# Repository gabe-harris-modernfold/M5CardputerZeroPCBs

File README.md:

# M5CardputerZeroPCBs

KiCad tooling for preparing PCB orders, driven from Claude Code through MCP servers.

## What's here

| Path | What it is |
| --- | --- |
| [`LightSensingPCB`](LightSensingPCB/README.md) | Cap carrying an Adafruit AS7343 14-channel spectral sensor breakout |
| [`BreadPortZero`](BreadPortZero/README.md) | Breakout cap: I2C (4 STEMMA QT / Qwiic, 2 sockets) on its own bus, buffered SPI, UART, 4 analog inputs (ADS1115) and USB-C supplemental power, with current limiting, a FAULT LED, a software power switch, I2C isolation and ESD protection for the host |
| [`tools/gerber_check`](tools/gerber_check/README.md) | `gerber-check`: checks Gerber and drill output against PCBWay and JLCPCB rules, lints the board and assembly files, and writes a ready-to-upload order package with an order sheet |
| `.mcp.json` | Registers three MCP servers for Claude Code: `kicad` (kicad-mcp-pro), `kicad-mixelpixx` (KiCAD-MCP-Server) and `gerber-check` |

## Setup (Windows)

- KiCad 10 installed in the default location (`kicad-cli` is used for exports and DRC). `gerber-check` and BreadPortZero's
  generators also find the per-user install that `winget install KiCad.KiCad` makes (`%LOCALAPPDATA%\Programs\KiCad\10.0`).
- [uv](https://docs.astral.sh/uv/) on `PATH`. `gerber-check` starts with `uv run`, which installs its dependencies on first use.
- Optional: `kicad-mcp-pro` installed with `uv tool install` (expected in `%USERPROFILE%\.local\bin`), and
  [KiCAD-MCP-Server](https://github.com/mixelpixx/KiCAD-MCP-Server) built in `C:\SourceCode\KiCAD-MCP-Server`.
- The paths in `.mcp.json` assume this repository is cloned to `C:\SourceCode\M5CardputerZeroPCBs`. Edit them if yours differs.

kicad-mcp-pro's first start can take about a minute, which is longer than Claude Code's default 30 s MCP startup
timeout. Set `MCP_TIMEOUT` (milliseconds) higher if it fails to connect.

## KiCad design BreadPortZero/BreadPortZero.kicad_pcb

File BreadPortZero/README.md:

# BreadPortZero

A cap for the M5Stack CardputerZero's top expansion port that adds:
- an I2C bus on four STEMMA QT / Qwiic connectors and two 0.1 in sockets;
- an SPI socket (SPI0, chip select CE1), buffered;
- a UART socket;
- four analog inputs, from an on-board ADS1115 ADC, with unfitted divider pads for 5 V signals;
- a USB-C jack for extra power: about 1 A at 3.3 V instead of about 220 mA from the host.

The host is protected in five ways:
- a current-limited power switch (234-303 mA), with a FAULT LED that lights while it limits, and a second one
  (1.09-1.26 A) on the USB input; a power mux connects only one source at a time, so neither can back-feed the other;
- an I2C isolator with ESD protection;
- an SPI buffer that keeps breadboard wiring off the display's bus and drops off it when the cap is unpowered;
- ESD protection on the SPI and UART lines, series resistors on the UART, series resistors and filter capacitors on
  the analog inputs;
- its own I2C bus on G22/G23, so external devices can't disturb the host's keyboard bus.

USB only powers the cap while the host's ExtPort 5 V is on. Bridge JP9 and a script can power-cycle everything plugged
in by driving G7 high (then the SPI socket can't be used).

The bottom silkscreen is the board's manual: setup steps (including the `config.txt` line), a ports table, the host
pinout beside every J1 pin, what each jumper does, a power-path diagram and what the LEDs mean.

See [SPEC.md](SPEC.md) for the design, pinout, solder jumpers, BOM and cost.

## Host setup

BreadPortZero's I2C bus is a software bus on G22 (SDA) / G23 (SCL). Add this to `/boot/firmware/config.txt`, reboot, and
turn on Settings > ExtPort:

```
dtoverlay=i2c-gpio,bus=3,i2c_gpio_sda=22,i2c_gpio_scl=23
```

The bus is `/dev/i2c-3`, and the ADS1115 answers at 0x48 (`i2cdetect -y 3`).

To put the bus on the host's I2C1 instead:
- Bridge JP1 and JP2.
- Cut JP8.
- Leave out the overlay.

To let software power-cycle the cap (for example to reset a hung I2C board), bridge JP9 and drive G7:

```
pinctrl set 7 op dh    # off
pinctrl set 7 op dl    # on
```

Hold it off for about a second so the rails drain. G7 is also the SPI socket's chip select (SPI0 CE1), which idles
high, so JP9 and SPI exclude each other: with JP9 bridged, keep the SPI driver off G7 (for example
`dtoverlay=spi0-1cs`).

The SPI socket is SPI0's CE1 (`/dev/spidev0.1`, if the host's image creates it alongside the display on CE0). Its
pins, left to right: GND, 3V3, SCK, MOSI, CS, MISO.

For more than about 220 mA at 3.3 V, plug a USB-C charger into the jack on the right end (power only; up to about 1 A
at 3.3 V). ExtPort 5 V must still be on.

The other jumpers are listed in [SPEC.md](SPEC.md#solder-jumpers).

## Files

| File | What it is |
| --- | --- |
| `BreadPortZero.kicad_pro`, `.kicad_sch`, `.kicad_pcb` | KiCad 10 project (generated; open and edit as usual) |
| `BreadPortZero.kicad_sym`, `sym-lib-table` | Project symbol library (TPS2553, TPS2116, TLV62569, 74LVC125: KiCad doesn't ship them in this form) |
| `BreadPortZero.pretty`, `fp-lib-table` | Project footprint library: the USB-C jack's KiCad footprint with fab-rule fixes |
| `tools/design.py` | Board size, pin maps, socket positions, parts and nets: the single source for both generators |
| `tools/gen_schematic.py` | Writes the schematic from `design.py` |
| `tools/gen_pcb.py` | Writes the PCB: placement, routing, fiducials, GND pours and silkscreen (including the bottom's reference text) |
| `tools/make_footprints.py` | Writes `BreadPortZero.pretty` from KiCad's stock footprints (run with KiCad's Python) |

## Rebuild

The scripts find KiCad 10 in `C:\Program Files\KiCad\10.0` or in the per-user location winget installs to
(`%LOCALAPPDATA%\Programs\KiCad\10.0`). Set `KICAD_DIR` to use another install.

```powershell
python tools\gen_schematic.py
```

```powershell
& "$env:LOCALAPPDATA\Programs\KiCad\10.0\bin\python.exe" tools\gen_pcb.py
```

Then check it:

```powershell
& "$env:LOCALAPPDATA\Programs\KiCad\10.0\bin\kicad-cli.exe" sch erc --severity-all BreadPortZero.kicad_sch
```

```powershell
& "$env:LOCALAPPDATA\Programs\KiCad\10.0\bin\kicad-cli.exe" pcb drc --schematic-parity --severity-all BreadPortZero.kicad_pcb
```

Regenerating overwrites hand edits to the schematic and PCB. Once you start editing in KiCad, stop using the generators.

The pictures in `docs/` are KiCad renders. `--side bottom` gives the bottom view; the 3D view is 952 high with
`--perspective --rotate "-45,0,20" --zoom 1.45`:

```powershell
& "$env:LOCALAPPDATA\Programs\KiCad\10.0\bin\kicad-cli.exe" pcb render --side top -w 1736 -h 504 --quality high --floor --zoom 1.9 -o docs\board-top.png BreadPortZero.kicad_pcb
```

Fab output comes from the `gerber-check` MCP server's `export_for_fab` tool (profile `jlcpcb_standard` or
`pcbway_standard`), which writes to `fab/<profile>/`.

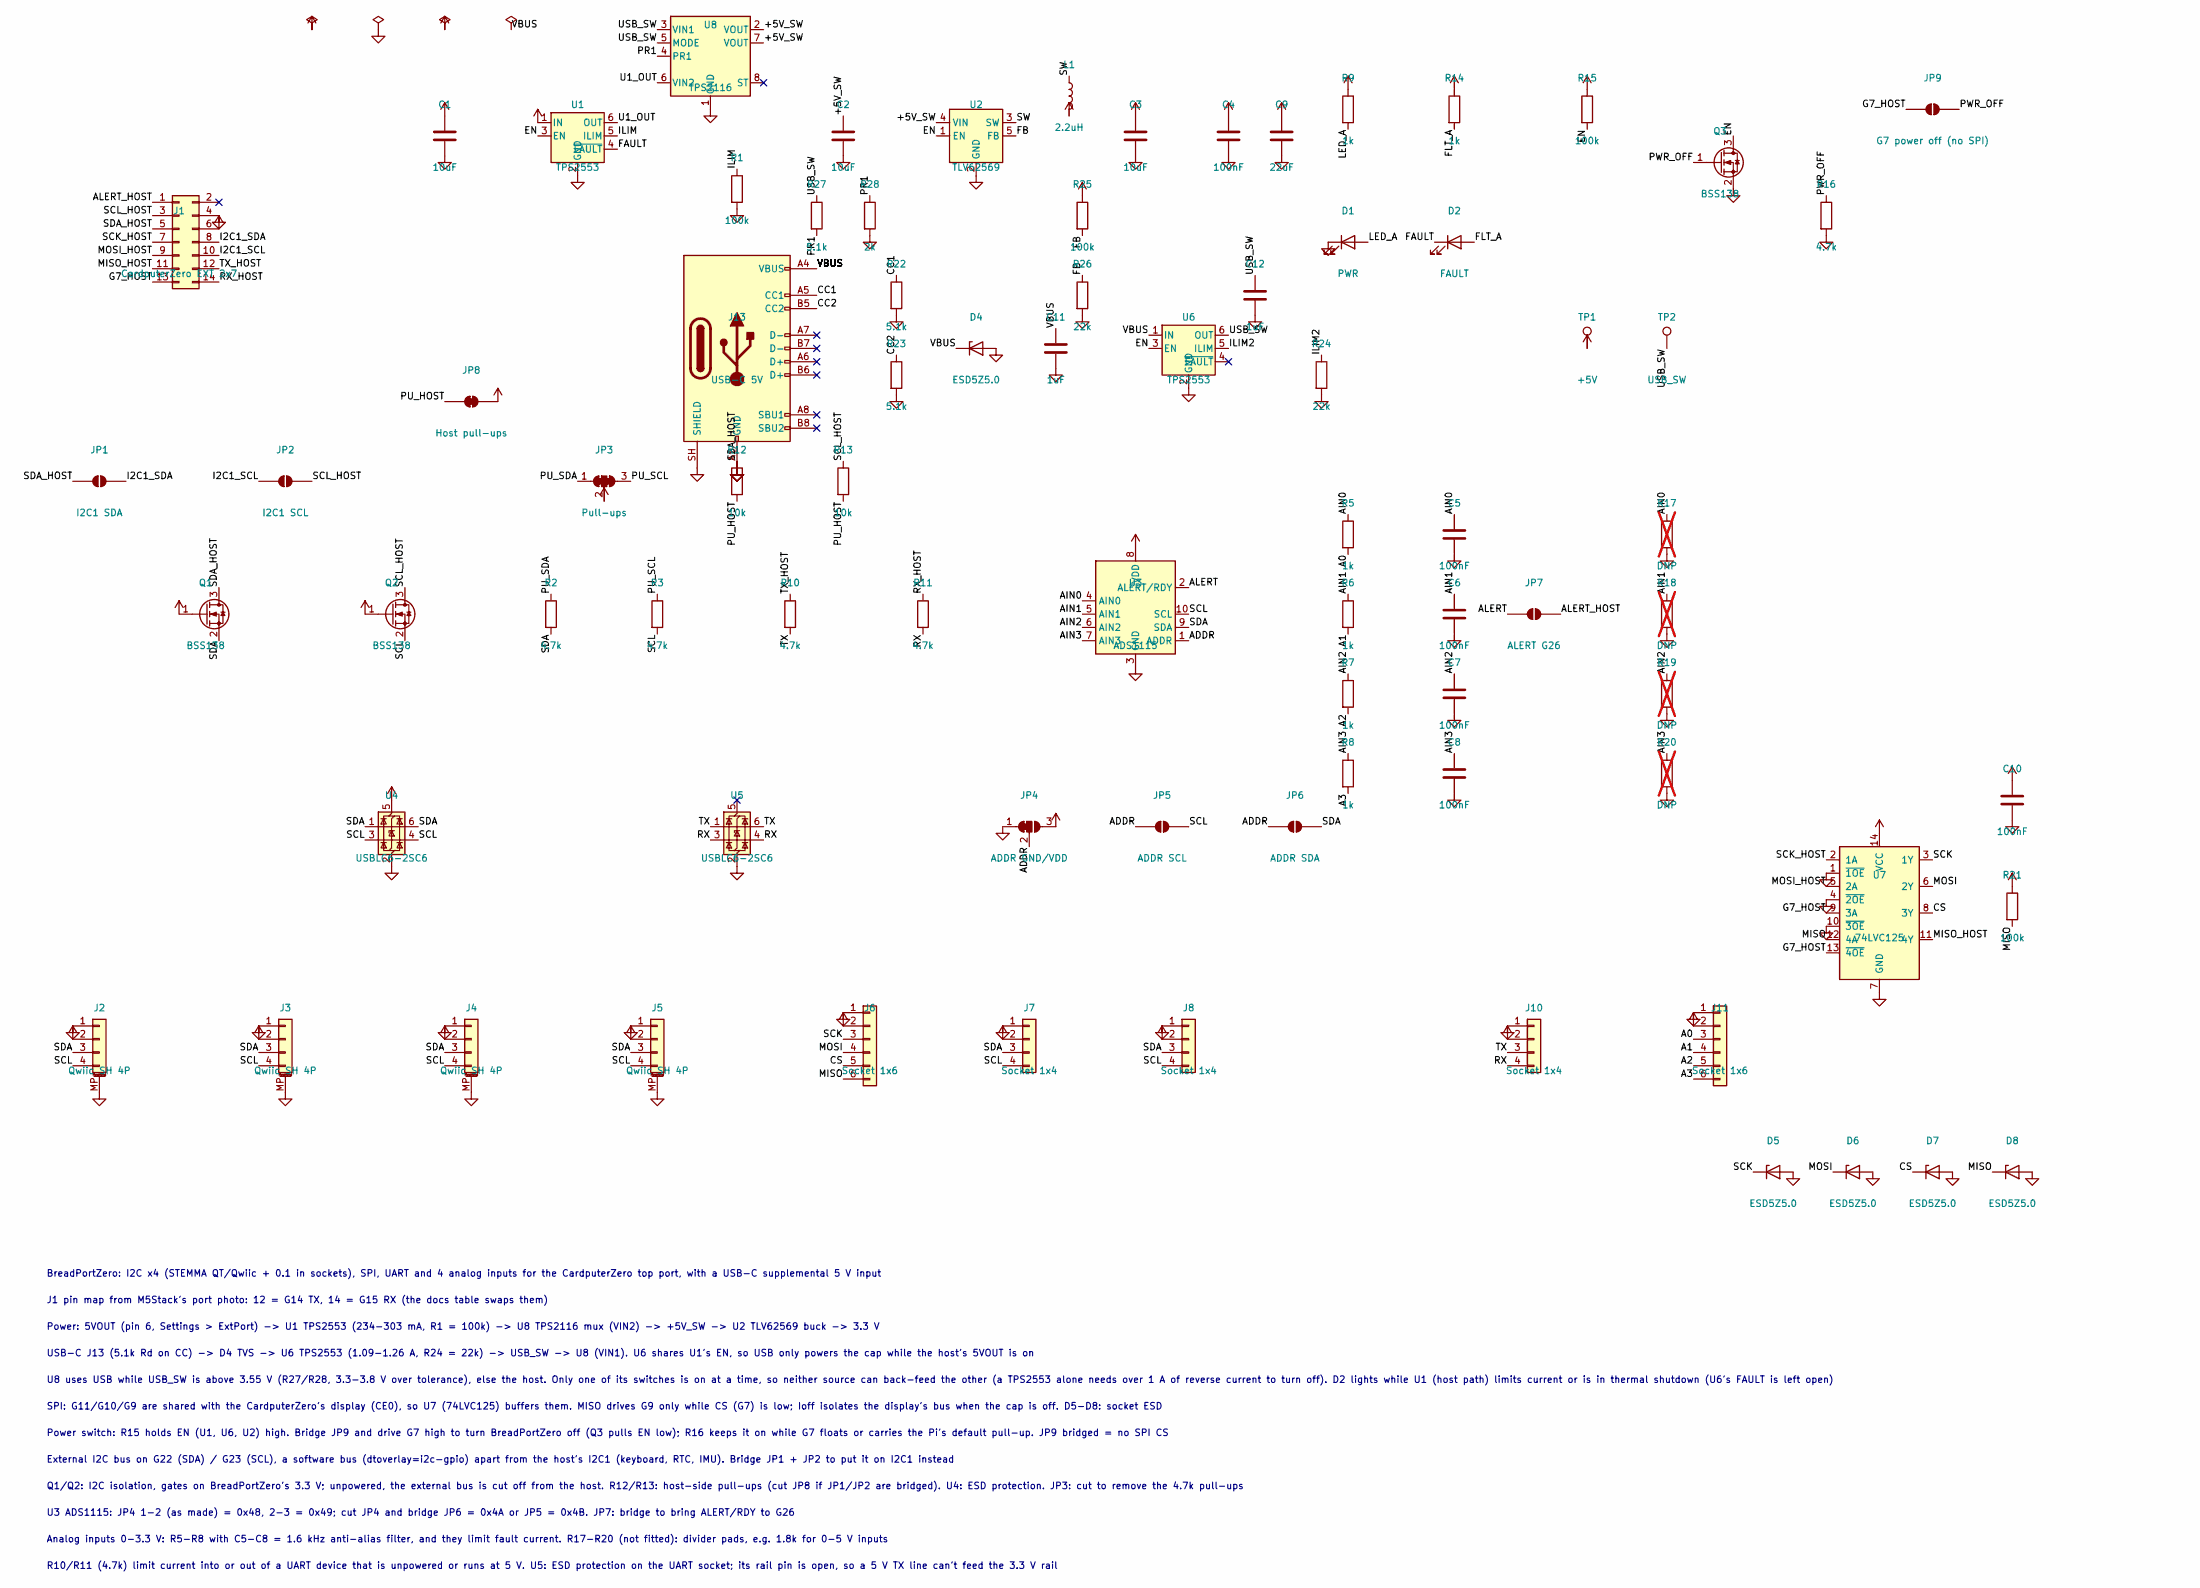
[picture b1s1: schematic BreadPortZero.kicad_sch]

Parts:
C1, C2, C3: 10uF; C_0805_2012Metric; MPN CL21A106KAYNNNE; LCSC C15850
C4, C10: 100nF; C_0603_1608Metric; MPN CC0603KRX7R9BB104; LCSC C14663
C5, C6, C7, C8: 100nF; C_0402_1005Metric; MPN CL05B104KO5NNNC; LCSC C1525
C9: 22uF; C_0805_2012Metric; MPN CL21A226MAQNNNE; LCSC C45783
C11, C12: 1uF; C_0402_1005Metric; MPN CL05A105KA5NQNC; LCSC C52923
D1: PWR; LED_0603_1608Metric; MPN 19-217/G7C-AN1P2/6T; LCSC C2986030
D2: FAULT; LED_0603_1608Metric; MPN KT-0603R; LCSC C2286
D4, D5, D6, D7, D8: ESD5Z5.0; D_SOD-523; MPN ESD5Z5.0T1G; LCSC C5199848
J1: CardputerZero EXT 2x7; PinHeader_2x07_P2.54mm_Vertical; MPN BOOMELE 2.54-2*7P; LCSC C71397
J2, J3, J4, J5: Qwiic SH 4P; JST_SH_BM04B-SRSS-TB_1x04-1MP_P1.00mm_Vertical; MPN Megastar ZX-SH1.0-4PLT; LCSC C7430453
J6, J11: Socket 1x6; PinSocket_1x06_P2.54mm_Vertical; MPN BOOMELE 2.54-1*6P; LCSC C40877
J7, J8, J10: Socket 1x4; PinSocket_1x04_P2.54mm_Vertical; MPN CONNFLY DS1023-1x4SF11; LCSC C7509546
J13: USB-C 5V; USB_C_Receptacle_HCTL_HC-TYPE-C-16P-01A_GNDTrim; MPN HC-TYPE-C-16P-01A; LCSC C2894897
JP1: I2C1 SDA; SolderJumper-2_P1.3mm_Open_RoundedPad1.0x1.5mm
JP2: I2C1 SCL; SolderJumper-2_P1.3mm_Open_RoundedPad1.0x1.5mm
JP3: Pull-ups; SolderJumper-3_P1.3mm_Bridged123_RoundedPad1.0x1.5mm
JP4: ADDR GND/VDD; SolderJumper-3_P1.3mm_Bridged12_RoundedPad1.0x1.5mm
JP5: ADDR SCL; SolderJumper-2_P1.3mm_Open_RoundedPad1.0x1.5mm
JP6: ADDR SDA; SolderJumper-2_P1.3mm_Open_RoundedPad1.0x1.5mm
JP7: ALERT G26; SolderJumper-2_P1.3mm_Open_RoundedPad1.0x1.5mm
JP8: Host pull-ups; SolderJumper-2_P1.3mm_Bridged_RoundedPad1.0x1.5mm
JP9: G7 power off (no SPI); SolderJumper-2_P1.3mm_Open_RoundedPad1.0x1.5mm
L1: 2.2uH; L_Changjiang_FTC252012S; MPN FTC252012S2R2MBCA; LCSC C5832372
Q1, Q2, Q3: BSS138; SOT-23; MPN BSS138LT1G; LCSC C82045
R1, R21: 100k; R_0603_1608Metric; MPN 0603WAF1003T5E; LCSC C25803
R2, R3, R10, R11, R16: 4.7k; R_0603_1608Metric; MPN 0603WAF4701T5E; LCSC C23162
R5, R6, R7, R8, R9, R14: 1k; R_0603_1608Metric; MPN 0603WAF1001T5E; LCSC C21190
R12, R13: 10k; R_0603_1608Metric; MPN 0603WAF1002T5E; LCSC C25804
R15, R25: 100k; R_0402_1005Metric; MPN 0402WGF1003TCE; LCSC C25741
R17, R18, R19, R20: DNP; R_0603_1608Metric; not fitted
R22, R23: 5.1k; R_0603_1608Metric; MPN 0603WAF5101T5E; LCSC C23186
R24, R26: 22k; R_0402_1005Metric; MPN 0402WGF2202TCE; LCSC C25768
R27: 5.1k; R_0402_1005Metric; MPN 0402WGF5101TCE; LCSC C25905
R28: 2k; R_0402_1005Metric; MPN 0402WGF2001TCE; LCSC C4109
TP1: +5V; TestPoint_Pad_D1.0mm
TP2: USB_SW; TestPoint_Pad_D1.0mm
U1, U6: TPS2553; SOT-23-6; MPN TPS2553DBVR; LCSC C55266
U2: TLV62569; SOT-23-5; MPN TLV62569DBVR; LCSC C141836
U3: ADS1115; MSOP-10_3x3mm_P0.5mm; MPN ADS1115IDGSR; LCSC C37593
U4, U5: USBLC6-2SC6; SOT-23-6; MPN USBLC6-2SC6; LCSC C7519
U7: 74LVC125; TSSOP-14_4.4x5mm_P0.65mm; MPN SN74LVC125APWR; LCSC C7813
U8: TPS2116; SOT-583-8; MPN TPS2116DRLR; LCSC C3235557

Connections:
+3V3: C3.1, C4.1, C9.1, C10.1, J2.2, J3.2, J4.2, J5.2, J6.2, J7.2, J8.2, J10.2, J11.2, JP3.2 (C), JP4.3 (B), JP8.2 (B), L1.2, Q1.1 (G), Q2.1 (G), R9.1, R21.1, R25.1, U3.8 (VDD), U4.5 (VBUS), U7.14 (VCC)
+5V: C1.1, J1.6, R14.1, R15.1, TP1.1, U1.1 (IN)
/+5V_SW: C2.1, U2.4 (VIN), U8.2 (VOUT), U8.7 (VOUT)
/A0: J11.3, R5.2
/A1: J11.4, R6.2
/A2: J11.5, R7.2
/A3: J11.6, R8.2
/ADDR: JP4.2 (C), JP5.1 (A), JP6.1 (A), U3.1 (ADDR)
/AIN0: C5.1, R5.1, R17.1, U3.4 (AIN0)
/AIN1: C6.1, R6.1, R18.1, U3.5 (AIN1)
/AIN2: C7.1, R7.1, R19.1, U3.6 (AIN2)
/AIN3: C8.1, R8.1, R20.1, U3.7 (AIN3)
/ALERT: JP7.1 (A), U3.2 (ALERT/RDY)
/ALERT_HOST: J1.1, JP7.2 (B)
/CC1: J13.A5 (CC1), R22.1
/CC2: J13.B5 (CC2), R23.1
/CS: D7.1 (K), J6.5, U7.8 (3Y)
/EN: Q3.3 (D), R15.2, U1.3 (EN), U2.1 (EN), U6.3 (EN)
/FAULT: D2.1 (K), U1.4 (~FAULT)
/FB: R25.2, R26.1, U2.5 (FB)
/FLT_A: D2.2 (A), R14.2
/G7_HOST: J1.13, JP9.1 (A), U7.9 (3A), U7.13 (~4OE)
/I2C1_SCL: J1.10, JP2.1 (A)
/I2C1_SDA: J1.8, JP1.2 (B)
/ILIM: R1.1, U1.5 (ILIM)
/ILIM2: R24.1, U6.5 (ILIM)
/LED_A: D1.2 (A), R9.2
/MISO: D8.1 (K), J6.6, R21.2, U7.12 (4A)
/MISO_HOST: J1.11, U7.11 (4Y)
/MOSI: D6.1 (K), J6.4, U7.6 (2Y)
/MOSI_HOST: J1.9, U7.5 (2A)
/PR1: R27.2, R28.1, U8.4 (PR1)
/PU_HOST: JP8.1 (A), R12.2, R13.2
/PU_SCL: JP3.3 (B), R3.1
/PU_SDA: JP3.1 (A), R2.1
/PWR_OFF: JP9.2 (B), Q3.1 (G), R16.1
/RX: J10.4, R11.2, U5.3 (I/O2), U5.4 (I/O2)
/RX_HOST: J1.14, R11.1
/SCK: D5.1 (K), J6.3, U7.3 (1Y)
/SCK_HOST: J1.7, U7.2 (1A)
/SCL: J2.4, J3.4, J4.4, J5.4, J7.4, J8.4, JP5.2 (B), Q2.2 (S), R3.2, U3.10 (SCL), U4.3 (I/O2), U4.4 (I/O2)
/SCL_HOST: J1.3, JP2.2 (B), Q2.3 (D), R13.1
/SDA: J2.3, J3.3, J4.3, J5.3, J7.3, J8.3, JP6.2 (B), Q1.2 (S), R2.2, U3.9 (SDA), U4.1 (I/O1), U4.6 (I/O1)
/SDA_HOST: J1.5, JP1.1 (A), Q1.3 (D), R12.1
/SW: L1.1, U2.3 (SW)
/TX: J10.3, R10.2, U5.1 (I/O1), U5.6 (I/O1)
/TX_HOST: J1.12, R10.1
/U1_OUT: U1.6 (OUT), U8.6 (VIN2)
/USB_SW: C12.1, R27.1, TP2.1, U6.6 (OUT), U8.3 (VIN1), U8.5 (MODE)
/VBUS: C11.1, D4.1 (K), J13.A4 (VBUS), J13.A9 (VBUS), J13.B4 (VBUS), J13.B9 (VBUS), U6.1 (IN)
GND: C1.2, C2.2, C3.2, C4.2, C5.2, C6.2, C7.2, C8.2, C9.2, C10.2, C11.2, C12.2, D1.1 (K), D4.2 (A), D5.2 (A), D6.2 (A), D7.2 (A), D8.2 (A), J1.4, J2.1, J2.MP (MountPin), J3.1, J3.MP (MountPin), J4.1, J4.MP (MountPin), J5.1, J5.MP (MountPin), J6.1, J7.1, J8.1, J10.1, J11.1, J13.A1 (GND), J13.A12 (GND), J13.B1 (GND), J13.B12 (GND), J13.SH (SHIELD), JP4.1 (A), Q3.2 (S), R1.2, R16.2, R17.2, R18.2, R19.2, R20.2, R22.2, R23.2, R24.2, R26.2, R28.2, U1.2 (GND), U2.2 (GND), U3.3 (GND), U4.2 (GND), U5.2 (GND), U6.2 (GND), U7.1 (~1OE), U7.4 (~2OE), U7.7 (GND), U7.10 (~3OE), U8.1 (GND)

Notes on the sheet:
BreadPortZero: I2C x4 (STEMMA QT/Qwiic + 0.1 in sockets), SPI, UART and 4 analog inputs for the CardputerZero top port, with a USB-C supplemental 5 V input
J1 pin map from M5Stack's port photo: 12 = G14 TX, 14 = G15 RX (the docs table swaps them)
Power: 5VOUT (pin 6, Settings > ExtPort) -> U1 TPS2553 (234-303 mA, R1 = 100k) -> U8 TPS2116 mux (VIN2) -> +5V_SW -> U2 TLV62569 buck -> 3.3 V
USB-C J13 (5.1k Rd on CC) -> D4 TVS -> U6 TPS2553 (1.09-1.26 A, R24 = 22k) -> USB_SW -> U8 (VIN1). U6 shares U1's EN, so USB only powers the cap while the host's 5VOUT is on
U8 uses USB while USB_SW is above 3.55 V (R27/R28, 3.3-3.8 V over tolerance), else the host. Only one of its switches is on at a time, so neither source can back-feed the other (a TPS2553 alone needs over 1 A of reverse current to turn off). D2 lights while U1 (host path) limits current or is in th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
SPI: G11/G10/G9 are shared with the CardputerZero's display (CE0), so U7 (74LVC125) buffers them. MISO drives G9 only while CS (G7) is low; Ioff isolates the display's bus when the cap is off. D5-D8: socket ESD
Power switch: R15 holds EN (U1, U6, U2) high. Bridge JP9 and drive G7 high to turn BreadPortZero off (Q3 pulls EN low); R16 keeps it on while G7 floats or carries the Pi's default pull-up. JP9 bridged = no SPI CS
External I2C bus on G22 (SDA) / G23 (SCL), a software bus (dtoverlay=i2c-gpio) apart from the host's I2C1 (keyboard, RTC, IMU). Bridge JP1 + JP2 to put it on I2C1 instead
Q1/Q2: I2C isolation, gates on BreadPortZero's 3.3 V; unpowered, the external bus is cut off from the host. R12/R13: host-side pull-ups (cut JP8 if JP1/JP2 are bridged). U4: ESD protection. JP3: cut to remove the 4.7k pull-ups
U3 ADS1115: JP4 1-2 (as made) = 0x48, 2-3 = 0x49; cut JP4 and bridge JP6 = 0x4A or JP5 = 0x4B. JP7: bridge to bring ALERT/RDY to G26
Analog inputs 0-3.3 V: R5-R8 with C5-C8 = 1.6 kHz anti-alias filter, and they limit fault current. R17-R20 (not fitted): divider pads, e.g. 1.8k for 0-5 V inputs
R10/R11 (4.7k) limit current into or out of a UART device that is unpowered or runs at 5 V. U5: ESD protection on the UART socket; its rail pin is open, so a 5 V TX line can't feed the 3.3 V rail

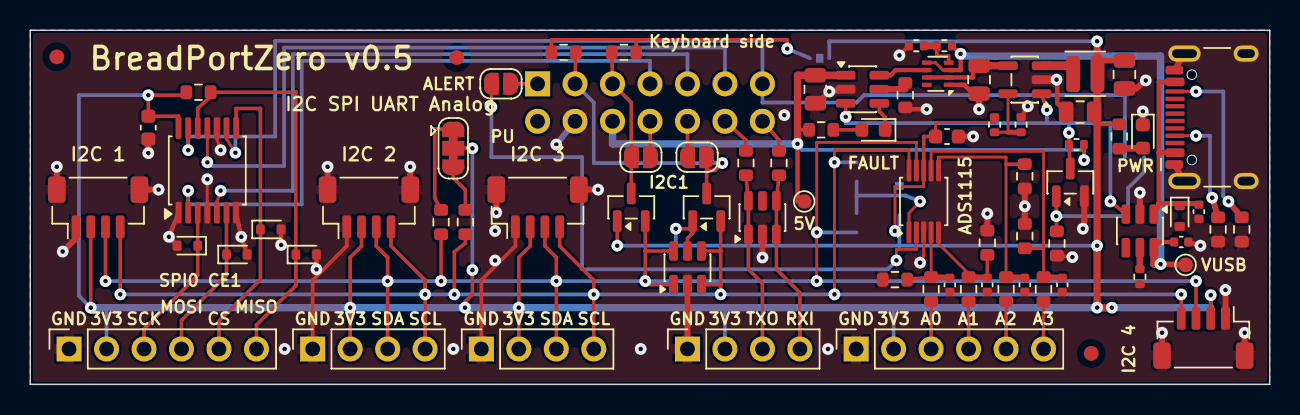
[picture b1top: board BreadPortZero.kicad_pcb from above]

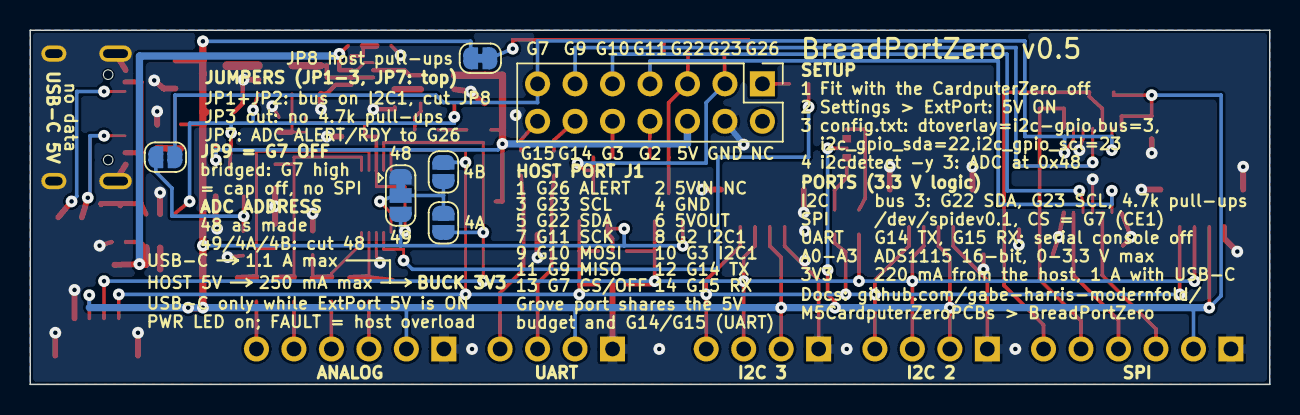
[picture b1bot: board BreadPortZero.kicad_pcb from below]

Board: 2 copper layers, 84.0 x 24.0 mm, 83 parts (6 on the bottom side), 51 nets.

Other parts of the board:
FID1, FID2, FID3: Fiducial_1mm_Mask2mm

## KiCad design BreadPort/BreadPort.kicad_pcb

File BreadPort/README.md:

# BreadPort

A cap for the M5Stack CardputerZero's top expansion port that breaks out the I2C bus to four STEMMA QT / Qwiic
connectors and four 0.1 in sockets, plus a UART socket and four analog inputs (on-board ADS1115 ADC). The host is
protected by a current-limited power switch and an I2C isolator. See [SPEC.md](SPEC.md) for the design, pinout, BOM
and cost.

## Files

| File | What it is |
| --- | --- |
| `BreadPort.kicad_pro`, `.kicad_sch`, `.kicad_pcb` | KiCad 10 project (generated; open and edit as usual) |
| `BreadPort.kicad_sym`, `sym-lib-table` | Project symbol library (SY6280AAC, which KiCad doesn't ship) |
| `tools/design.py` | Board size, pin maps, socket positions, parts and nets: the single source for both generators |
| `tools/gen_schematic.py` | Writes the schematic from `design.py` |
| `tools/gen_pcb.py` | Writes the PCB: placement, routing, fiducials and GND pours |

## Rebuild

The scripts find KiCad 10 in `C:\Program Files\KiCad\10.0` or in the per-user location winget installs to
(`%LOCALAPPDATA%\Programs\KiCad\10.0`). Set `KICAD_DIR` to use another install.

```powershell
python tools\gen_schematic.py
```

```powershell
& "$env:LOCALAPPDATA\Programs\KiCad\10.0\bin\python.exe" tools\gen_pcb.py
```

Then check it:

```powershell
& "$env:LOCALAPPDATA\Programs\KiCad\10.0\bin\kicad-cli.exe" sch erc --severity-all BreadPort.kicad_sch
```

```powershell
& "$env:LOCALAPPDATA\Programs\KiCad\10.0\bin\kicad-cli.exe" pcb drc --schematic-parity --severity-all BreadPort.kicad_pcb
```

Regenerating overwrites hand edits to the schematic and PCB. Once you start editing in KiCad, stop using the generators.

Fab output comes from the `gerber-check` MCP server's `export_for_fab` tool (profile `jlcpcb_standard` or
`pcbway_standard`), which writes to `fab/<profile>/`.

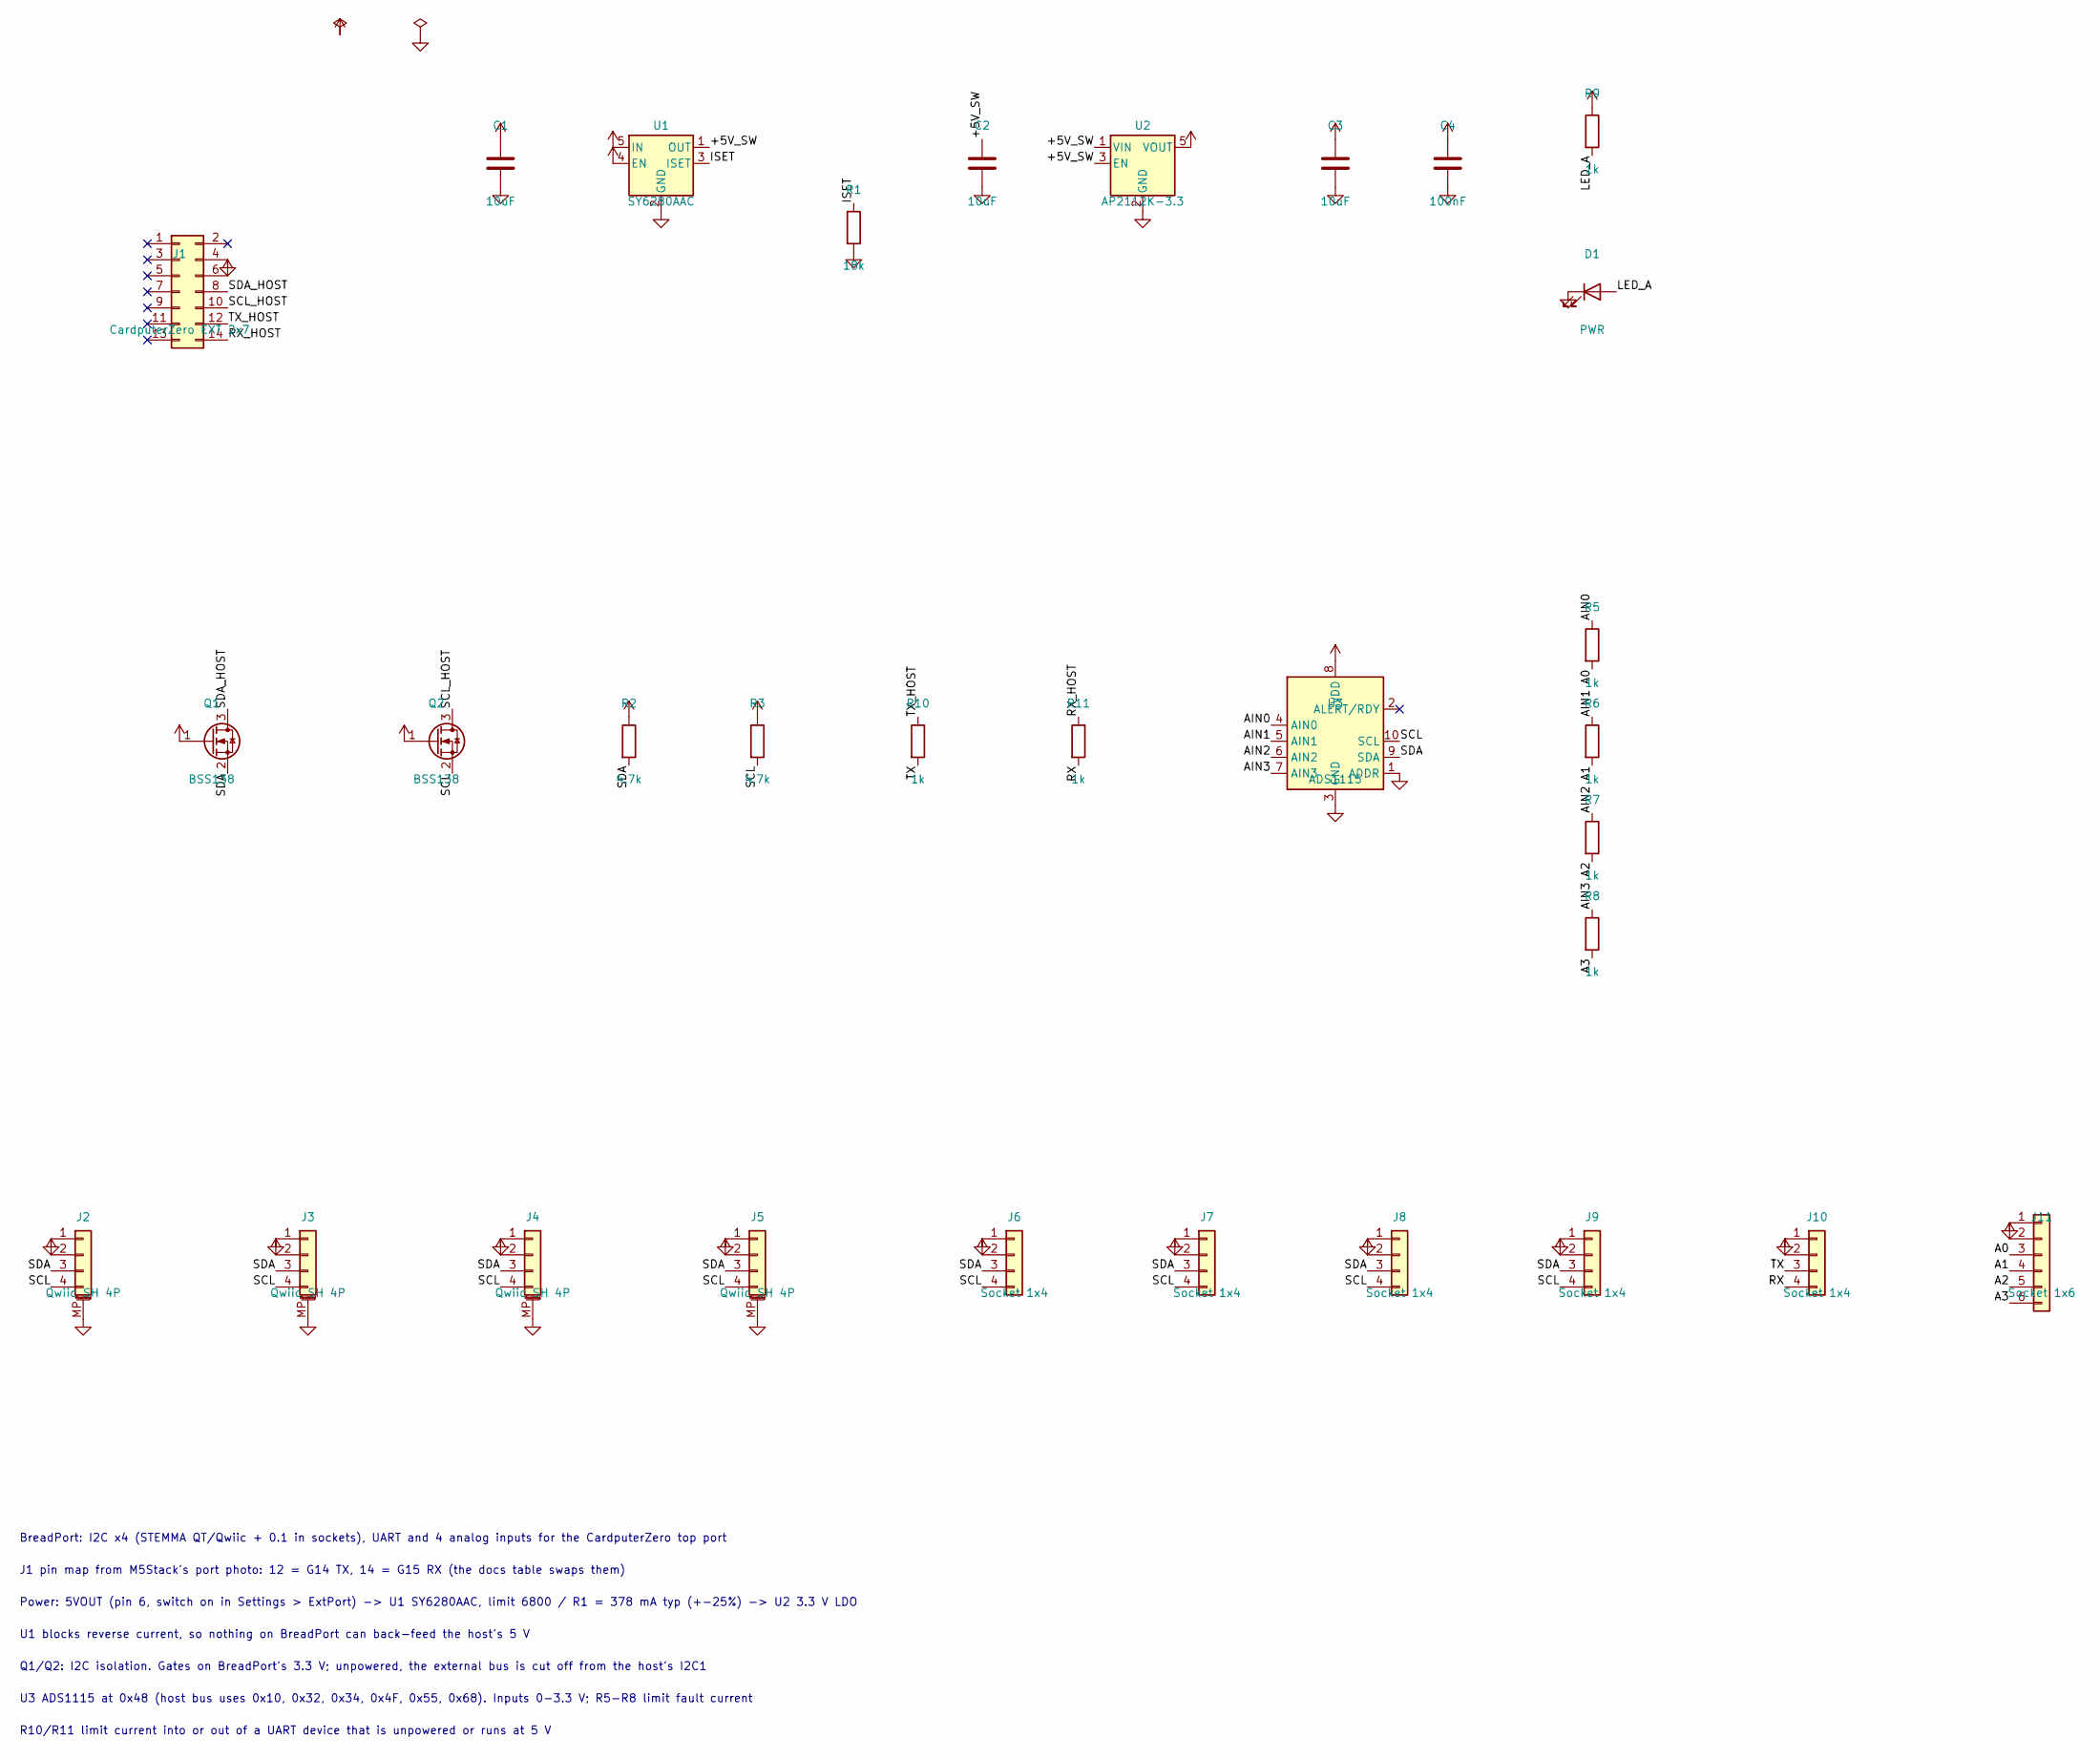
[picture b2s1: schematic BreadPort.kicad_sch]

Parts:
C1, C2, C3: 10uF; C_0805_2012Metric; MPN CL21A106KAYNNNE; LCSC C15850
C4: 100nF; C_0603_1608Metric; MPN CC0603KRX7R9BB104; LCSC C14663
D1: PWR; LED_0603_1608Metric; MPN 19-217/G7C-AN1P2/6T; LCSC C2986030
J1: CardputerZero EXT 2x7; PinHeader_2x07_P2.54mm_Vertical; MPN BOOMELE 2.54-2*7P; LCSC C71397
J2, J3, J4, J5: Qwiic SH 4P; JST_SH_BM04B-SRSS-TB_1x04-1MP_P1.00mm_Vertical; MPN Megastar ZX-SH1.0-4PLT; LCSC C7430453
J6, J7, J8, J9, J10: Socket 1x4; PinSocket_1x04_P2.54mm_Vertical; MPN CONNFLY DS1023-1x4SF11; LCSC C7509546
J11: Socket 1x6; PinSocket_1x06_P2.54mm_Vertical; MPN BOOMELE 2.54-1*6P; LCSC C40877
Q1, Q2: BSS138; SOT-23; MPN BSS138LT1G; LCSC C82045
R1: 18k; R_0603_1608Metric; MPN 0603WAF1802T5E; LCSC C25810
R2, R3: 4.7k; R_0603_1608Metric; MPN 0603WAF4701T5E; LCSC C23162
R5, R6, R7, R8, R9, R10, R11: 1k; R_0603_1608Metric; MPN 0603WAF1001T5E; LCSC C21190
U1: SY6280AAC; SOT-23-5; MPN SY6280AAC; LCSC C55136
U2: AP2112K-3.3; SOT-23-5; MPN AP2112K-3.3TRG1; LCSC C51118
U3: ADS1115; MSOP-10_3x3mm_P0.5mm; MPN ADS1115IDGSR; LCSC C37593

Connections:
+3V3: C3.1, C4.1, J2.2, J3.2, J4.2, J5.2, J6.2, J7.2, J8.2, J9.2, J10.2, J11.2, Q1.1 (G), Q2.1 (G), R2.1, R3.1, R9.1, U2.5 (VOUT), U3.8 (VDD)
+5V: C1.1, J1.6, U1.4 (EN), U1.5 (IN)
/+5V_SW: C2.1, U1.1 (OUT), U2.1 (VIN), U2.3 (EN)
/A0: J11.3, R5.2
/A1: J11.4, R6.2
/A2: J11.5, R7.2
/A3: J11.6, R8.2
/AIN0: R5.1, U3.4 (AIN0)
/AIN1: R6.1, U3.5 (AIN1)
/AIN2: R7.1, U3.6 (AIN2)
/AIN3: R8.1, U3.7 (AIN3)
/ISET: R1.1, U1.3 (ISET)
/LED_A: D1.2 (A), R9.2
/RX: J10.4, R11.2
/RX_HOST: J1.14, R11.1
/SCL: J2.4, J3.4, J4.4, J5.4, J6.4, J7.4, J8.4, J9.4, Q2.2 (S), R3.2, U3.10 (SCL)
/SCL_HOST: J1.10, Q2.3 (D)
/SDA: J2.3, J3.3, J4.3, J5.3, J6.3, J7.3, J8.3, J9.3, Q1.2 (S), R2.2, U3.9 (SDA)
/SDA_HOST: J1.8, Q1.3 (D)
/TX: J10.3, R10.2
/TX_HOST: J1.12, R10.1
GND: C1.2, C2.2, C3.2, C4.2, D1.1 (K), J1.4, J2.1, J2.MP (MountPin), J3.1, J3.MP (MountPin), J4.1, J4.MP (MountPin), J5.1, J5.MP (MountPin), J6.1, J7.1, J8.1, J9.1, J10.1, J11.1, R1.2, U1.2 (GND), U2.2 (GND), U3.1 (ADDR), U3.3 (GND)

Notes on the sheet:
BreadPort: I2C x4 (STEMMA QT/Qwiic + 0.1 in sockets), UART and 4 analog inputs for the CardputerZero top port
J1 pin map from M5Stack's port photo: 12 = G14 TX, 14 = G15 RX (the docs table swaps them)
Power: 5VOUT (pin 6, switch on in Settings > ExtPort) -> U1 SY6280AAC, limit 6800 / R1 = 378 mA typ (+-25%) -> U2 3.3 V LDO
U1 blocks reverse current, so nothing on BreadPort can back-feed the host's 5 V
Q1/Q2: I2C isolation. Gates on BreadPort's 3.3 V; unpowered, the external bus is cut off from the host's I2C1
U3 ADS1115 at 0x48 (host bus uses 0x10, 0x32, 0x34, 0x4F, 0x55, 0x68). Inputs 0-3.3 V; R5-R8 limit fault current
R10/R11 limit current into or out of a UART device that is unpowered or runs at 5 V

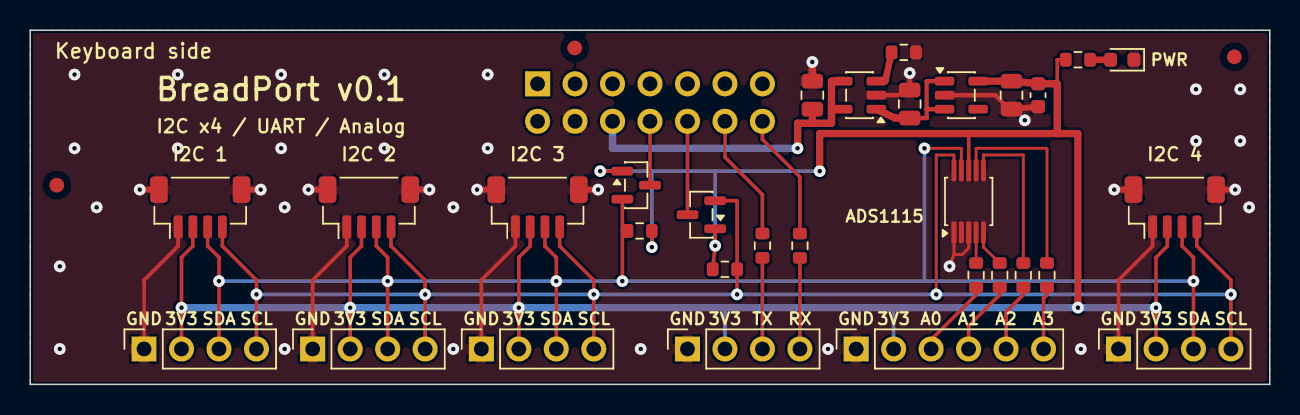
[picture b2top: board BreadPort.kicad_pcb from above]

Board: 2 copper layers, 84.0 x 24.0 mm, 34 parts (1 on the bottom side), 22 nets.

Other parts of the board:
FID1, FID2, FID3: Fiducial_1mm_Mask2mm

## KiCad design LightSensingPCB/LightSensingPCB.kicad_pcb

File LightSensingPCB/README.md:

# LightSensingPCB

A cap for the M5Stack CardputerZero's top expansion port that carries an Adafruit AS7343 14-channel spectral sensor
breakout. See [SPEC.md](SPEC.md) for the design, pinout, BOM and cost.

## Files

| File | What it is |
| --- | --- |
| `LightSensingPCB.kicad_pro`, `.kicad_sch`, `.kicad_pcb` | KiCad 10 project (generated; open and edit as usual) |
| `tools/design.py` | Board size, pin maps, parts and nets: the single source for both generators |
| `tools/gen_schematic.py` | Writes the schematic from `design.py` |
| `tools/gen_pcb.py` | Writes the PCB: placement, routing and GND pours |

## Rebuild

```powershell
python tools\gen_schematic.py
```

```powershell
& "C:\Program Files\KiCad\10.0\bin\python.exe" tools\gen_pcb.py
```

Then check it:

```powershell
& "C:\Program Files\KiCad\10.0\bin\kicad-cli.exe" pcb drc --schematic-parity --severity-all LightSensingPCB.kicad_pcb
```

Regenerating overwrites hand edits to the schematic and PCB. Once you start editing in KiCad, stop using the generators.

Fab output comes from the `gerber-check` MCP server's `export_for_fab` tool (profile `jlcpcb_standard` or
`pcbway_standard`), which writes to `fab/<profile>/`.

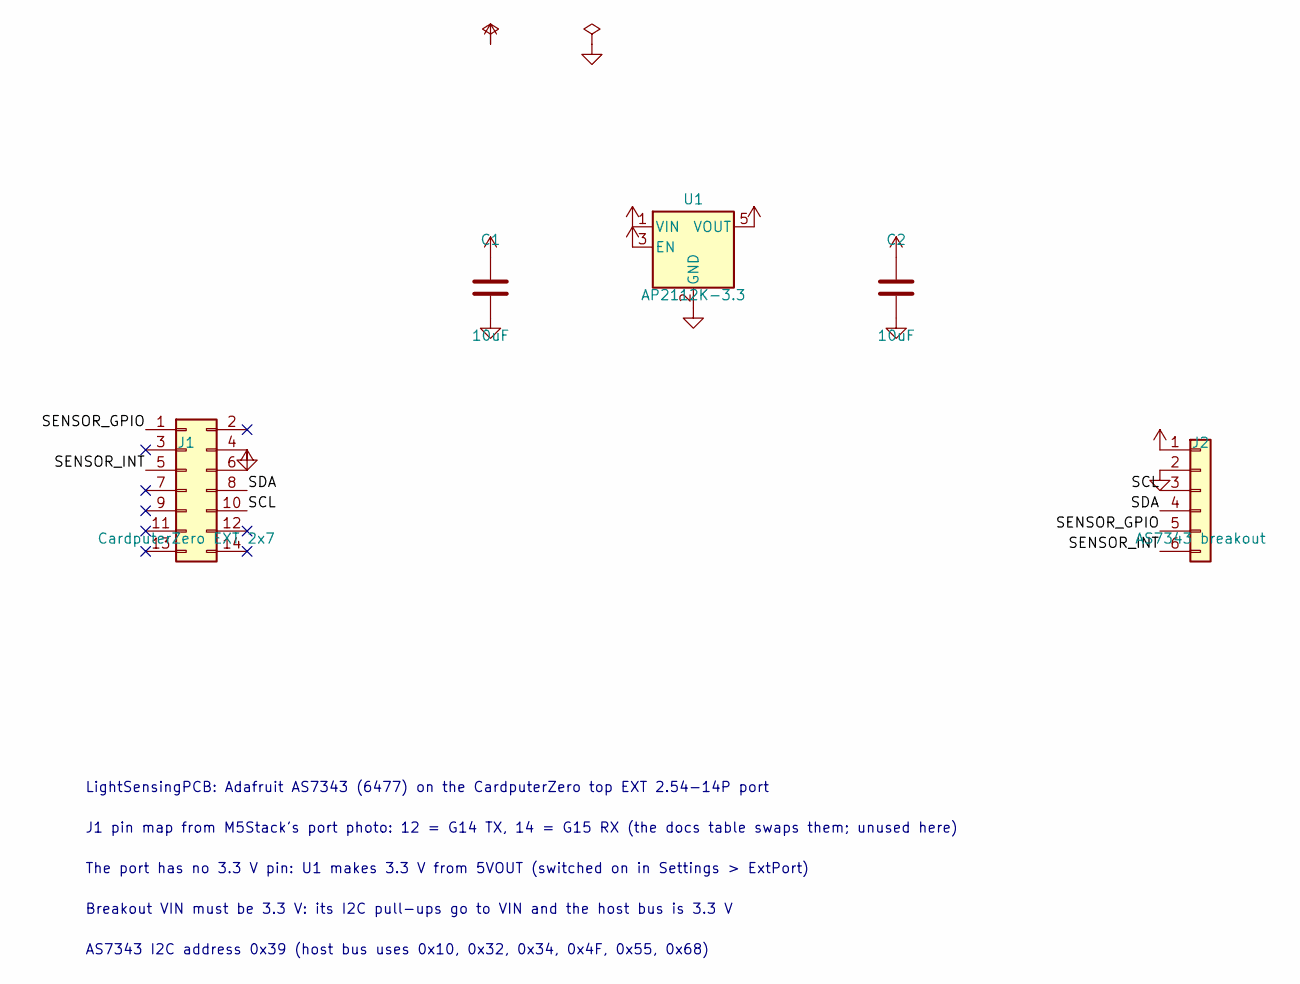
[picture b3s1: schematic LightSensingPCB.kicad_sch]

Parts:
C1, C2: 10uF; C_0805_2012Metric; MPN CL21A106KAYNNNE; LCSC C15850
J1: CardputerZero EXT 2x7; PinHeader_2x07_P2.54mm_Vertical; MPN BOOMELE 2.54-2*7P; LCSC C71397
J2: AS7343 breakout; PinSocket_1x06_P2.54mm_Vertical; MPN BOOMELE 2.54-1*6P; LCSC C40877
U1: AP2112K-3.3; SOT-23-5; MPN AP2112K-3.3TRG1; LCSC C51118

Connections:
+3V3: C2.1, J2.1, U1.5 (VOUT)
+5V: C1.1, J1.6, U1.1 (VIN), U1.3 (EN)
/SCL: J1.10, J2.3
/SDA: J1.8, J2.4
/SENSOR_GPIO: J1.1, J2.5
/SENSOR_INT: J1.5, J2.6
GND: C1.2, C2.2, J1.4, J2.2, U1.2 (GND)

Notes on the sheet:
LightSensingPCB: Adafruit AS7343 (6477) on the CardputerZero top EXT 2.54-14P port
J1 pin map from M5Stack's port photo: 12 = G14 TX, 14 = G15 RX (the docs table swaps them; unused here)
The port has no 3.3 V pin: U1 makes 3.3 V from 5VOUT (switched on in Settings > ExtPort)
Breakout VIN must be 3.3 V: its I2C pull-ups go to VIN and the host bus is 3.3 V
AS7343 I2C address 0x39 (host bus uses 0x10, 0x32, 0x34, 0x4F, 0x55, 0x68)

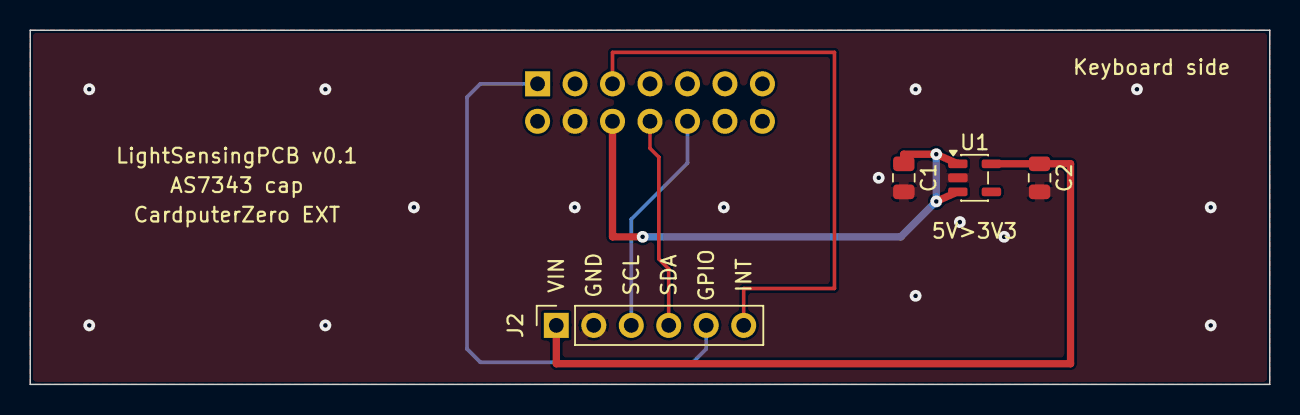
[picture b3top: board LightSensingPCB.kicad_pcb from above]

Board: 2 copper layers, 84.0 x 24.0 mm, 5 parts (1 on the bottom side), 7 nets.

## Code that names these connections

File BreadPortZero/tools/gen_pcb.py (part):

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               and abs(pad_xy("JP3", 1)[0] - PU_X) < 0.01)                # PU_SDA top, 3V3 middle, PU_SCL bottom
vertical("R2", PU_X - 0.825, 13.0, pin1_up=True)
vertical("R3", PU_X + 0.825, 13.0, pin1_up=True)
horizontal("JP7", COL[0] - 2.48, D.J1_ODD_Y)            # pad 1 ALERT, pad 2 ALERT_HOST next to pin 1

# SPI block between Qwiic 1 and Qwiic 2. U7 (74LVC125) has its pin rows top (VCC 4OE 4A 4Y 3OE 3A 3Y) and bottom
# (1OE 1A 1Y 2OE 2A 2Y GND): host lines come in on the bottom layer to vias under it, SCK/MOSI leave down from the
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# +3V3 (C3) -> the trunk (x 72.3). The buck's feedback divider (R25/R26) and output cap sit under it.
vertical("C1", 53.2, 4.0, pin1_up=True)                 # +5V on top
place_oriented("U1", 56.4, 4.0, lambda: pad_xy("U1", 1)[0] < 56.4 and pad_xy("U1", 1)[1] < 4.0)  # IN top-left
vertical("R1", 59.3, 4.4, pin1_up=True)                # ILIM on top
# Power mux where the two 5 V paths meet. Left column (top to bottom): MODE, VIN2 (host), VOUT, ST; right column:
# PR1, VIN1 (USB), VOUT, GND. Its threshold divider sits above it, along the top edge.
U8_X, U8_Y = 61.5, 2.95
place_oriented("U8", U8_X, U8_Y, lambda: pad_xy("U8", 5)[0] < U8_X and pad_xy("U8", 5)[1] < U8_Y)   # MODE top-left
horizontal("R27", 61.95, 1.05, pin1_left=False)        # pad 1 (USB_SW) right, pad 2 (PR1) left; courtyards 0.58 mm
horizontal("R28", 60.05, 1.05, pin1_left=False)        # from the edge. Pad 1 (PR1) right, pad 2 (GND) left
vertical("C2", 64.3, 3.35, pin1_up=True)                # +5V_SW on top
U2_X, U2_Y = 67.4, 3.35
place_oriented("U2", U2_X, U2_Y, lambda: pad_xy("U2", 4)[0] < U2_X and pad_xy("U2", 4)[1] < U2_Y)  # VIN top-left
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vertical("R26", 67.15, 6.4, pin1_up=False)              # FB bottom, GND top
# right of the trunk, beside the jack: bulk cap, PWR LED
vertical("C9", 74.15, 3.0, pin1_up=True)
vertical("R9", 73.8, 7.2, pin1_up=True)                 # +3V3 top, LED_A bottom
vertical("D1", 75.4, 7.2, pin1_up=True)                 # cathode top, anode bottom
# USB-C jack in the top-right corner, opening to the right edge (front face 1 mm past it); Qwiic 4 below it
J13_X, J13_Y = D.BOARD_W + 1.0 - 3.675, 5.9
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place_oriented("U6", U6_X, U6_Y, lambda: pad_xy("U6", 1)[0] > U6_X and pad_xy("U6", 1)[1] < U6_Y)
vertical("D4", 77.9, 12.6, pin1_up=True)                # cathode (VBUS) up
vertical("C11", 79.2, 12.3, pin1_up=True)               # VBUS up
horizontal("C12", 78.0, 14.35)                          # pad 1 (USB_SW) left, towards U6's OUT pin
vertical("R24", U6_X, 16.7, pin1_up=True)               # ILIM up
vertical("R22", 80.5, 13.5, pin1_up=True)               # CC1 up
vertical("R23", 82.1, 13.5, pin1_up=True)               # CC2 up
horizontal("JP9", 74.84, 8.6)                           # bottom: pad 1 (G7) left, pad 2 (PWR_OFF) right
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place("TP1", 52.45, 11.6)
place("TP2", 78.3, 15.9)

# ADC: pins 6-10 (AIN2, AIN3, VDD, SDA, SCL) face up, 1-5 (ADDR, ALERT, GND, AIN0, AIN1) face down, ADDR at the
# bottom-left. x puts AIN0 straight above the A0 socket pin.
A_X = [pad_xy("J11", n)[0] for n in (3, 4, 5, 6)]       # A0-A3 socket pins
ADC_X, ADC_Y = A_X[0] - 0.5, 11.6
place_oriented("U3", ADC_X, ADC_Y, lambda: pad_xy("U3", 1)[0] < ADC_X and pad_xy("U3", 1)[1] > ADC_Y)
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               and abs(pad_xy("JP6", 1)[0] - JPA_X) < 0.01)          # ADDR top, SDA bottom
# Divider pads (unfitted), each next to its AINx node: R17 left of R5, R18 above C6, R19/R20 between the AIN2 and
# AIN3 tracks
horizontal("R17", A_X[0] - 2.45, RC_Y - 0.65, pin1_left=False)       # pad 1 (AIN0) towards R5
vertical("R18", A_X[1] + 1.27, 14.4, pin1_up=False)                  # pad 1 (AIN1) down to C6
DIV_X = (A_X[2] + A_X[3]) / 2
vertical("R19", DIV_X, 9.9, pin1_up=True)                            # pad 1 (AIN2) up, GND down
vertical("R20", DIV_X, 13.95, pin1_up=False)                         # pad 1 (AIN3) down, GND up

# Power switch between the AIN3 track and the 3V3 trunk: R15 (EN pull-up, 0402) above Q3 (drain up), R16 below
Q3_X = (A_X[3] + 72.3) / 2
horizontal("R15", 70.9, 7.75, pin1_left=False)                       # pad 1 +5V right, pad 2 EN over Q3's drain
place_oriented("Q3", Q3_X, 10.31, lambda: pad_xy("Q3", 3)[1] < 10.31 and pad_xy("Q3", 1)[0] < Q3_X)
vertical("R16", pad_xy("Q3", 1)[0] + 0.04, 14.45, pin1_up=True)      # pad 1 (PWR_OFF) under Q3's gate

# Fiducials for pick-and-place (U3 is 0.5 mm pitch): board-only, no schematic symbol, not in the BOM
for i, (x, y) in enumerate([(1.8, 1.8), (71.9, 21.9), (28.9, 1.85)], 1):
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via("GND", *gq4)

# --- host side of the bus ---
# G22 (SDA_HOST): pin 5 through the channel between pins 6 and 8, JP1 pad 1, Q1 drain (top)
track("SDA_HOST", F, [j1[5], (CH[2], ROW_MID), pad("JP1", 1), pad("Q1", 3)])
# G2 (I2C1_SDA) to JP1 pad 2; G3 (I2C1_SCL) to JP2 pad 1 (top)
track("I2C1_SDA", F, [j1[8], pad("JP1", 2)])
track("I2C1_SCL", F, [j1[10], pad("JP2", 1)])
# G23 (SCL_HOST): pin 3 on the bottom through the channel between pins 4 and 6, under JP1/JP2, up to Q2's drain
G23_Y = 9.0
g23v = (SCL_X + 1.06, G23_Y)
track("SCL_HOST", B, [j1[3], (CH[1], ROW_MID), (CH[1], G23_Y), g23v])
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    sx, sy = pad("J10", sock)
    bx = u5[bot][0]
    track(sig, F, [pad(r, 2), u5[top], u5[bot], (bx, UART_JOG_Y), (sx, UART_JOG_Y + abs(sx - bx)), (sx, sy)])
# U5's rail pin (5) is left open (see design.py). Its GND pin: down to a via between the spine and the ALERT run
u5g = (u5[2][0], 15.4)
track("GND", F, [u5[2], u5g], 0.4)
via("GND", *u5g)
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via("USB_SW", *usv)
track("USB_SW", F, [usv, (usv[0], u8[3][1]), u8[3]], 0.3)
track("USB_SW", F, [u8[3], (61.85, u8[3][1]), (61.85 - (u8[3][1] - u8[5][1]), u8[5][1]), u8[5]], FINE)
SWV2 = (76.6, 15.85)                                    # USB_SW from U6's OUT pin
track("USB_SW", B, [usv, (usv[0] + SWB_Y - usv[1], SWB_Y), (SWV2[0], SWB_Y), SWV2], 0.5)
via("USB_SW", *SWV2)
# Mux output: its two VOUT pins joined under the package, then round to C2 (+5V_SW) and the buck's VIN. Its GND pin
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gvd = (DIV_X, (dv["R19"][2][1] + dv["R20"][2][1]) / 2)
track("GND", F, [dv["R19"][2], gvd, dv["R20"][2]], 0.4)
via("GND", *gvd)
# GND pin to a via below it; ALERT down, left to a via, then on the bottom to JP7 by J1 pin 1
gvu = (u3[3][0] - 0.25, 15.75)
track("GND", F, [u3[3], (u3[3][0], gvu[1] - 0.45), gvu], FINE)
via("GND", *gvu)
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track("GND", F, [r16[2], gr16])
via("GND", *gr16)

# J1's GND pin is boxed in on the bottom by G23 and ALERT: tie it to a via so it doesn't hang on one thermal spoke
gj = (j1[4][0] - 1.27, 7.75)
track("GND", B, [j1[4], gj], 0.4)
via("GND", *gj)
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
